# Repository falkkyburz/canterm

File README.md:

# CAN Termination

This is a D-SUB 9 standard CAN pinout terminaton adapter. It inserts a 120 Ohm resistor between the CAN-H and CAN-L signals.

## BOM

I also included the interactive html BOM (canterm.html) 

| References     | Value                     | Footprint | Quantity |
|----------------|---------------------------|-----------|----------|
| R1             | 120R                      | 1206      | 1        |
| R2 - R10       | 0R                        | 1206      | 9        |
| J1             | DB9 Male                  |           | 1        |
| J2             | DB9 Female                |           | 1        |

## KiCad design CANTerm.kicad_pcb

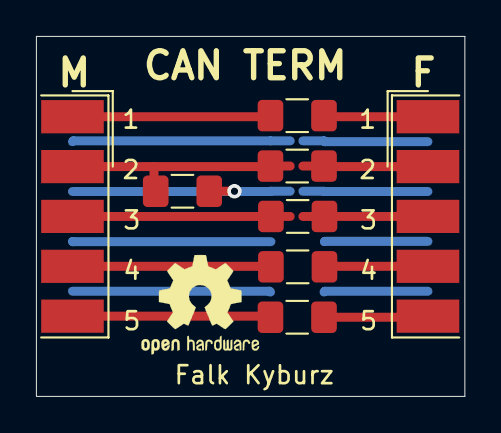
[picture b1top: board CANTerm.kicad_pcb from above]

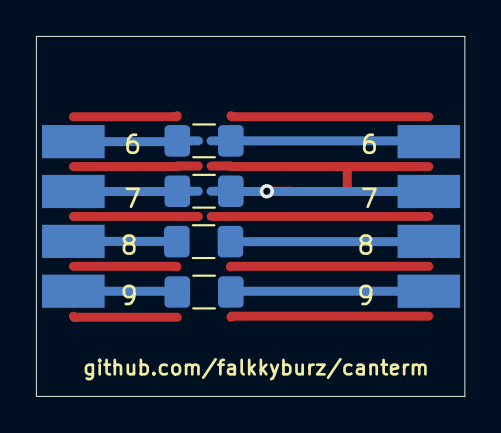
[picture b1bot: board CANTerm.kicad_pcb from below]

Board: 2 copper layers, 23.8 x 20.0 mm, 12 parts (4 on the bottom side), 18 nets.

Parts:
J1: DB9_Male; DSUB-9_Male_EdgeMount_P2.77mm
J2: DB9_Female; DSUB-9_Female_EdgeMount_P2.77mm
R1: 120; R_1206_3216Metric_Pad1.42x1.75mm_HandSolder
R2, R3, R4, R5, R6, R7, R8, R9, R10: 0; R_1206_3216Metric_Pad1.42x1.75mm_HandSolder

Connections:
/5V_0: J1.1, R2.2
/5V_1: J1.9, R9.2
/CAN_H: J1.7, R1.2, R5.2
/CAN_L: J1.2, R1.1, R4.2
/GND_0: J1.6, R3.2
/GND_1: J1.3, R6.2
/NC2: J1.5, R10.2
/NC_0: J1.8, R7.2
/NC_1: J1.4, R8.2
unnamed: J2.1, R2.1
unnamed: J2.2, R4.1
unnamed: J2.3, R6.1
unnamed: J2.4, R8.1
unnamed: J2.5, R10.1
unnamed: J2.6, R3.1
unnamed: J2.7, R5.1
unnamed: J2.8, R7.1
unnamed: J2.9, R9.1

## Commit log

2021-06-13 Updated silk screen and added traces to bridge jumpers with solder.
2021-06-13 Fixed spelling
